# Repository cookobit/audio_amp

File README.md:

# TPA3251 Audio Amplifier (Current main rev v0.1a)

Repository has an amplifier board under development for self entertainment and for self studies.

### Initial targets:
With this project I want to achieve the following:

1. The output THD + N should remain low: **<0.1%**. 

    * The solution of capturing this measurement requires personal research. The metric is specified.
2. Make the amplifier sound good!
3. Learn the design process and learn the tools over the project advancement.
4. Learn how to design filters.

---
### Hardware requirements:

* Amplifier circuit (Done)
* Pre-amplifier circuit
* UI (indicator LEDs, volume control)
* 2x speaker output ports
* 1x USB-C Input interface --> DAC module integration (might develop my own one, if interested)
* 1x 3.5mm Input
* 1x Power Flip Switch (I always wanted such)
---
#### Defined Characteristics:
V = 24V - 36V (most cases) 

#### Power tree: 
36V TPA3251_PVDD
  --> 15V 
    --> 12V TPA3251_VDD
      --> 3.3V LEDs, (MCU?)
      
(might require 5V)

---
### Known issues:
1. Buck converter wrong connection
2. Indicator LED driver MOSFETs have a wrong arrangement
3. Update LM5010-12 footprint (at the moment its for the *-8.0)
---
# Future development as of 5th of March, 2026

Consider using 4-layer board --> miniturize
Start designing pre-amplifier and volume control

1. LTSpice pre-amp circuit with volume control. (Bass..?)
2. After pre amp circuit is done and valid, add the UI terminal in circuit. (Interfaces, LED indicators)
3. After UI, DAC module, Bluetooth?
4. Controlling MCU + flash option.
5. Update the board design. Merge updates.

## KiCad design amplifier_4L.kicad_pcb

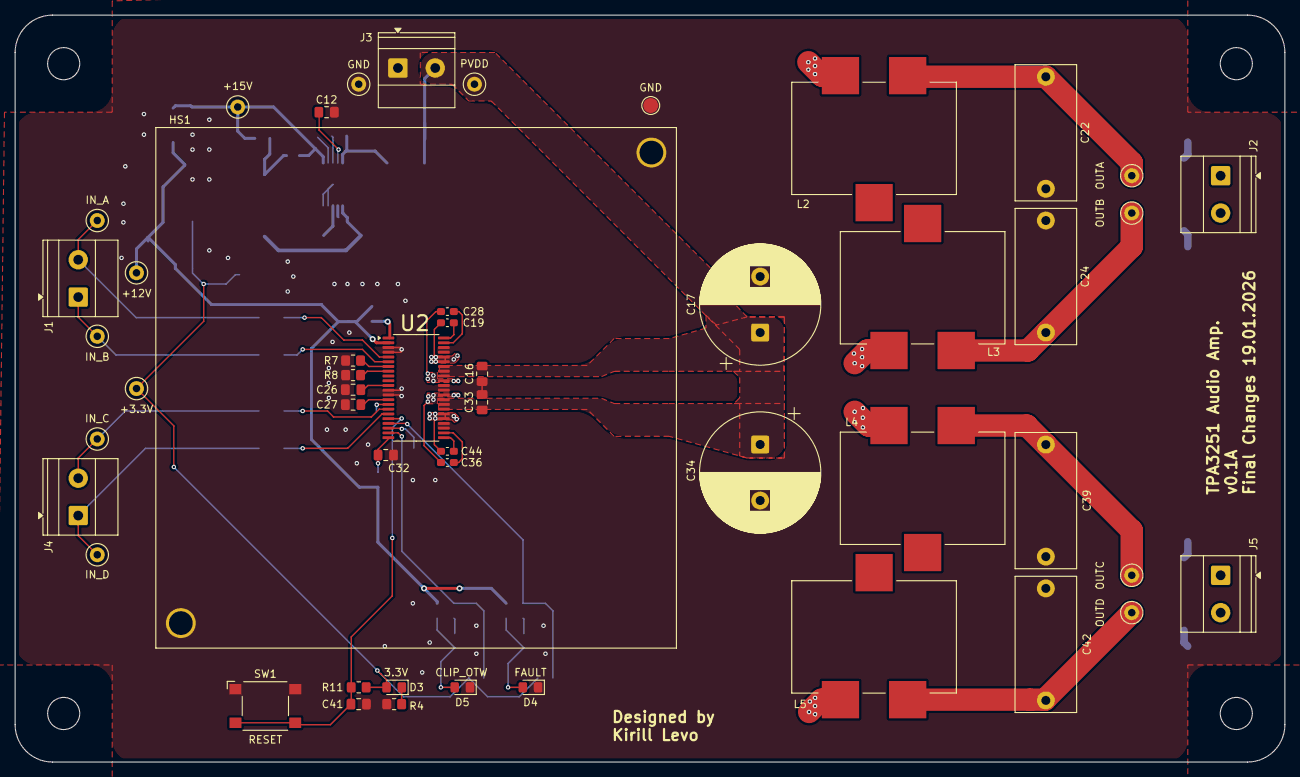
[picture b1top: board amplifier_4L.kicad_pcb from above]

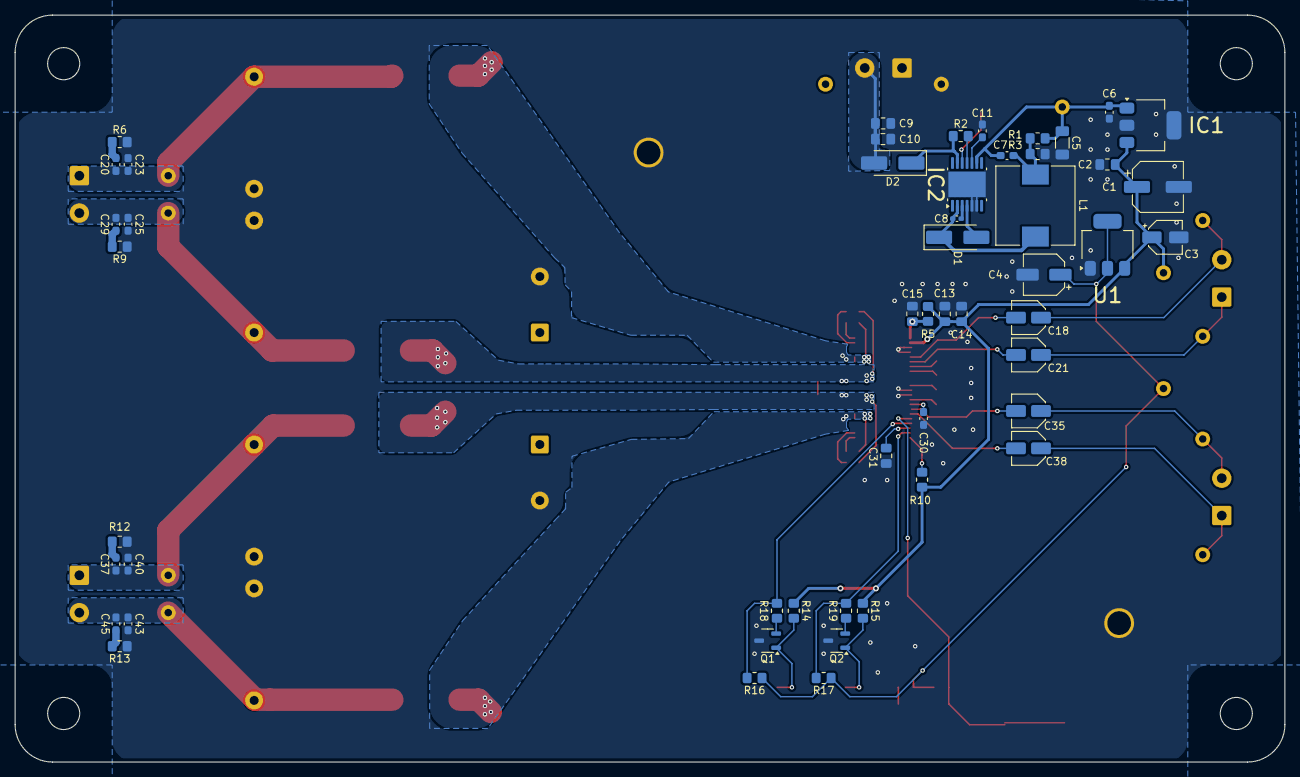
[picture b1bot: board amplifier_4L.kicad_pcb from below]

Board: 2 copper layers, 170.0 x 100.0 mm, 101 parts (51 on the bottom side), 53 nets.

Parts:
+3.3V, +12V, +15V: TestPoint; TestPoint_Loop_D2.50mm_Drill1.0mm_LowProfile
C1: 47u; CP_Elec_6.3x5.9
C2: 0.1u; C_0805_2012Metric_Pad1.18x1.45mm_HandSolder
C3: 10u; CP_Elec_4x5.4
C4: 100u; CP_Elec_5x5.9
C5: 4.7u; C_1206_3216Metric_Pad1.33x1.80mm_HandSolder
C6: 470n; C_0603_1608Metric_Pad1.08x0.95mm_HandSolder
C7: 5600p; C_0603_1608Metric_Pad1.08x0.95mm_HandSolder
C8: 47n; C_0402_1005Metric_Pad0.74x0.62mm_HandSolder
C9: 2.2u; C_0805_2012Metric_Pad1.18x1.45mm_HandSolder
C10, C12, C14, C15, C31, C32, C41: 100n; C_0805_2012Metric_Pad1.18x1.45mm_HandSolder
C11: 4.7n; C_0603_1608Metric_Pad1.08x0.95mm_HandSolder
C13, C16, C26, C27, C33: 1u; C_0805_2012Metric_Pad1.18x1.45mm_HandSolder
C17, C34: 1000u; CP_Radial_D16.0mm_P7.50mm
C18, C21, C35, C38: 10u; C_Elec_4x5.4
C19, C28, C36, C44: 33n; C_0603_1608Metric_Pad1.08x0.95mm_HandSolder
C20, C29, C30, C37, C45: 10n; C_0603_1608Metric_Pad1.08x0.95mm_HandSolder
C22, C24, C39, C42: 1u; C_Rect_L18.0mm_W8.0mm_P15.00mm_FKS3_FKP3
C23, C25, C40, C43: 1n; C_0603_1608Metric_Pad1.08x0.95mm_HandSolder
D1: 100V/1A; D_SMA_Handsoldering
D2: 100V/3A; D_SMA_Handsoldering
D3: Green - Power; LED_0805_2012Metric_Pad1.15x1.40mm_HandSolder
D4: Red - Fault; LED_0805_2012Metric_Pad1.15x1.40mm_HandSolder
D5: Orange - OTW; LED_0805_2012Metric_Pad1.15x1.40mm_HandSolder
GND: TestPoint; TestPoint_Loop_D2.50mm_Drill1.0mm_LowProfile
GND#2: TestPoint_Pad_D2.0mm
HS1: Heatsink_Pad_2Pin; HSINK_HSB38-707025P
IC1: LM2940IMPX-8.0_NOPB; SOT-223
IC2: LM5010MH_NOPB; Texas_HTSSOP-14-1EP_4.4x5mm_P0.65mm_EP3.4x5mm_Mask3.155x3.2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
IN_A: TestPoint; TestPoint_Loop_D2.50mm_Drill1.0mm_LowProfile
IN_B: TestPoint; TestPoint_Loop_D2.50mm_Drill1.0mm_LowProfile
IN_C: TestPoint; TestPoint_Loop_D2.50mm_Drill1.0mm_LowProfile
IN_D: TestPoint; TestPoint_Loop_D2.50mm_Drill1.0mm_LowProfile
J1, J2, J3, J4, J5: Screw_Terminal_01x02; TerminalBlock_Phoenix_MKDS-1,5-2_1x02_P5.00mm_Horizontal
L1: 100uH 1.5A; L_10.4x10.4_H4.8
L2, L3, L4, L5: 10u; L_Wuerth_HCF-2013
OUTA: TestPoint; TestPoint_Loop_D2.50mm_Drill1.0mm_LowProfile
OUTB: TestPoint; TestPoint_Loop_D2.50mm_Drill1.0mm_LowProfile
OUTC: TestPoint; TestPoint_Loop_D2.50mm_Drill1.0mm_LowProfile
OUTD: TestPoint; TestPoint_Loop_D2.50mm_Drill1.0mm_LowProfile
PVDD: TestPoint; TestPoint_Loop_D2.50mm_Drill1.0mm_LowProfile
Q1, Q2: NMOS; SOT-23-3
R1: 4.99k; R_0805_2012Metric_Pad1.20x1.40mm_HandSolder
R2: 182k; R_0805_2012Metric_Pad1.20x1.40mm_HandSolder
R3, R14, R15: 1k; R_0805_2012Metric_Pad1.20x1.40mm_HandSolder
R4: 499; R_0805_2012Metric_Pad1.20x1.40mm_HandSolder
R5, R6, R9, R10, R12, R13: 3R3; R_0805_2012Metric_Pad1.20x1.40mm_HandSolder
R7: 22k; R_0805_2012Metric_Pad1.20x1.40mm_HandSolder
R8: 10k; R_0805_2012Metric_Pad1.20x1.40mm_HandSolder
R11, R16, R17: 47k; R_0805_2012Metric_Pad1.20x1.40mm_HandSolder
R18, R19: 100; R_0805_2012Metric_Pad1.20x1.40mm_HandSolder
SW1: SW_Push; SW_SPST_Omron_B3FS-100xP
U1: TLV1117-33; SOT-223-3_TabPin2
U2: TPA3251; HTSSOP-44_6.1x14mm_P0.635mm_TopEP4.14x7.01mm

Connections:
+3.3V: +3.3V.1, C4.1, D3.2 (A), R11.1, R16.1, R17.1, U1.2 (VO)
+12V: +12V.1, C1.1, C2.1, C3.1, C13.2, C14.2, IC1.3 (OUT), R5.1, R10.1, R14.1, R15.1, U1.3 (VI), U2.2 (VDD)
+15V: +15V.1, C5.1, C6.1, C7.1, IC1.1 (IN), IC2.9 (FB), R1.1
/CLIP_OTW: R17.2, R19.1, U2.21 (~CLIP_OTW)
/FAULT: R16.2, R18.1, U2.19 (~FAULT)
/OUTA: C20.2, C22.1, C23.1, J2.1, L2.2, OUTA.1
/OUTB: C24.2, C25.2, C29.2, J2.2, L3.2, OUTB.1
/OUTC: C37.2, C39.1, C40.1, J5.1, L4.2, OUTC.1
/OUTD: C42.2, C43.2, C45.2, J5.2, L5.2, OUTD.1
/Orange: D5.2 (A), Q2.1 (D), R15.2
/PWMA: C19.2, L2.1, U2.39 (OUT_A), U2.40 (OUT_A)
/PWMB: C28.1, L3.1, U2.35 (OUT_B)
/PWMC: C36.2, L4.1, U2.32 (OUT_C)
/PWMD: C44.1, L5.1, U2.27 (OUT_D), U2.28 (OUT_D)
/RESET: C41.1, R11.2, SW1.2, U2.18 (~RESET)
/Red: D4.2 (A), Q1.1 (D), R14.2
/input_a: C18.1, IN_A.1, J1.2
/input_b: C21.1, IN_B.1, J1.1
/input_c: C35.1, IN_C.1, J4.2
/input_d: C38.1, IN_D.1, J4.1
GND: C1.2, C2.2, C3.2, C4.2, C5.2, C6.2, C9.2, C10.2, C11.2, C12.2, C13.1, C14.1, C15.1, C16.1, C17.2, C22.2, C23.2, C24.1, C25.1, C26.1, C27.1, C30.1, C31.1, C32.1, C33.1, C34.2, C39.2, C40.2, C41.2, C42.1, C43.1, D4.1 (K), D5.1 (K), GND.1, GND#2.1, HS1.1, HS1.2, IC1.2 (GND), IC1.4 (PAD), IC2.5 (SGND), IC2.6 (RTN), IC2.15 (EP), J3.1, Q1.3 (S), Q2.3 (S), R3.2, R4.2, R6.2, R7.1, R8.1, R9.1, R12.2, R13.1, SW1.1, U1.1 (GND), U2.3 (M1), U2.4 (M2), U2.12 (GND), U2.13 (GND), U2.25 (GND), U2.26 (GND), U2.33 (GND), U2.34 (GND), U2.41 (GND), U2.42 (GND)
unnamed: C7.2, L1.2, R1.2, R3.1
unnamed: C20.1, R6.1
unnamed: C29.1, R9.2
unnamed: C37.1, R12.1
unnamed: C45.1, R13.2
unnamed: D1.2 (A), IC2.4 (ISEN)
unnamed: C8.1, D1.1 (K), IC2.2 (SW), L1.1
unnamed: D2.1 (K), IC2.13 (VIN), R2.1
unnamed: D3.1 (K), R4.1
unnamed: C8.2, IC2.3 (BST)
unnamed: IC2.11 (RON/SD), R2.2
unnamed: C11.1, IC2.10 (SS)
unnamed: C12.1, IC2.12 (VCC)
unnamed: Q1.2 (G), R18.2
unnamed: Q2.2 (G), R19.2
unnamed: C27.2, U2.14 (AVDD)
unnamed: C19.1, U2.44 (BST_A)
unnamed: C28.2, U2.43 (BST_B)
unnamed: C30.2, U2.15 (C_START)
unnamed: C26.2, U2.11 (DVDD)
unnamed: R8.2, U2.8 (FREQ_ADJ)
unnamed: C15.2, R5.2, U2.1 (GVDD_AB)
unnamed: C18.2, U2.5 (INPUT_A)
unnamed: C21.2, U2.6 (INPUT_B)
unnamed: R7.2, U2.7 (OC_ADJ)
unnamed: C31.2, U2.20 (VBG)
unnamed: C36.1, U2.24 (BST_C)
unnamed: C44.2, U2.23 (BST_D)
unnamed: C32.2, R10.2, U2.22 (GVDD_CD)
unnamed: C35.2, U2.16 (INPUT_C)
unnamed: C38.2, U2.17 (INPUT_D)
PVDD: C9.1, C10.1, C16.2, C17.1, C33.2, C34.1, D2.2 (A), J3.2, PVDD.1, U2.29 (PVDD_CD), U2.30 (PVDD_CD), U2.31 (PVDD_CD), U2.36 (PVDD_AB), U2.37 (PVDD_AB), U2.38 (PVDD_AB)

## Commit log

2026-03-05 Initial commit after starting the usage of version control
2026-03-05 Restructure and renaming
2026-03-05 Create README.md
    Created a README. Description, targets, structure.
2026-03-05 Update README.md
    Description for 4 layer board
2026-03-05 Update README.md
    Minor README note
2026-03-06 Update README.md
    Plan update
2026-03-13 Initial commit: 4-layer amp PCB project in KiCad. LTspice simulation of preamp + filtering
